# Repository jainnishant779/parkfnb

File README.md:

# ParkFNB

Smart parking for India: owners list their space, drivers book it, and a camera + barrier
at the gate lets the right car in automatically.

## Repo layout

| Folder | What lives here |
|---|---|
| [`research/`](research/) | Market and tech studies, product requirements, pitch deck, proposals, status reports |
| [`hardware/`](hardware/) | ESP32 barrier firmware and the deployment / hardware plan |
| [`ai/`](ai/) | ANPR (number-plate + bay detection) service and its experiments, parking space optimizer |
| [`software/`](software/) | Consumer and owner apps, admin panel, landing page, marketing website, Node backend |

Start with [`software/README.md`](software/README.md) for how to run the apps and backend,
and [`software/docs/system-design.md`](software/docs/system-design.md) for the architecture.

Secrets (`.env`, keys, model weights) are never committed â€” see [`.gitignore`](.gitignore).

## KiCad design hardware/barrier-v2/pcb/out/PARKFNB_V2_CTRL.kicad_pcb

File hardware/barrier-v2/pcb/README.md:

# PARKFNB V2 controller PCB

100 x 80 mm, 2 layers, all through-hole. ESP32 DevKit V1 + 74AHCT125 level shift + sense/protection for the IBT-2.
Motor current does not flow through this board (battery -> fuse -> switch -> IBT-2 directly).

## Files (`out/`)
| File | Use |
|---|---|
| `PARKFNB_V2_Controller_PCB.pdf` | 7 sheets: spec, schematic, top/bottom views, drill table, wiring, bring-up, netlist |
| `PARKFNB_V2_CTRL.kicad_pcb` | KiCad 8 board (placed + routed, GND plane as an unfilled zone) |
| `gerbers/`, `PARKFNB_V2_CTRL_gerbers.zip` | Gerber + Excellon drill, ready for a fab |
| `PARKFNB_V2_CTRL_BOM.csv`, `..._netlist.csv` | BOM and netlist |

## Rebuild
```
pip install shapely numpy matplotlib kiutils gerbonara
python build.py     # route + DRC + export + verify
python report.py    # also rebuilds the PDF
```
Edit `placement.py` (positions) or `design.py` (parts, nets, footprints) and re-run.

## What was verified (and what was not)
Verified here: own DRC (clearance 0.25, edge, annular ring, hole-to-hole, keep-outs, opens, GND plane), the
`.kicad_pcb` parsed with kiutils and connectivity rebuilt independently (no shorts / opens), every Gerber and drill
file re-read with gerbonara and rendered.

NOT verified: KiCad itself was not available. Open the board in KiCad, press **B** (fill zones), run **Inspect > DRC**.
Footprints are generic through-hole footprints from standard pitches: check each one against the real part
(ESP32 header row spacing 25.4 vs 22.86, buzzer pitch, screw terminal, PTC, electrolytics, TVS/diode lead drill).
No thermal, EMC or in-shell test has been done.

## Rev A changes (V2 scope)
- Three position sensors for the 0 - 90 - 180 deg motion: J4 = 0 deg (GPIO32), J10 = 90 deg / locked (GPIO13),
  J5 = 180 deg (GPIO33). All Hall sensors run on 5 V with open-collector outputs pulled up to 3V3.
- Battery = the V1 4 x 18650 holder (assumed 4S, 16.8 V full): TVS P6KE20A, divider 100k/18k (16.8 V -> 2.56 V).
  Input range 7-17 V, so a 2S pack also works.

## Firmware
See sheet 1 of the PDF: new pins are GPIO27 (motor enable), 13/32/33 (0/90/180 deg sensors), 35 (battery ADC),
4 (red LED), 23 (tamper). `config.h` today clamps motion to 0-90 deg; 0-90-180 needs a firmware change.
With a 4S pack limit PWM_MAX to ~180 so the 12 V motor sees ~12 V average.

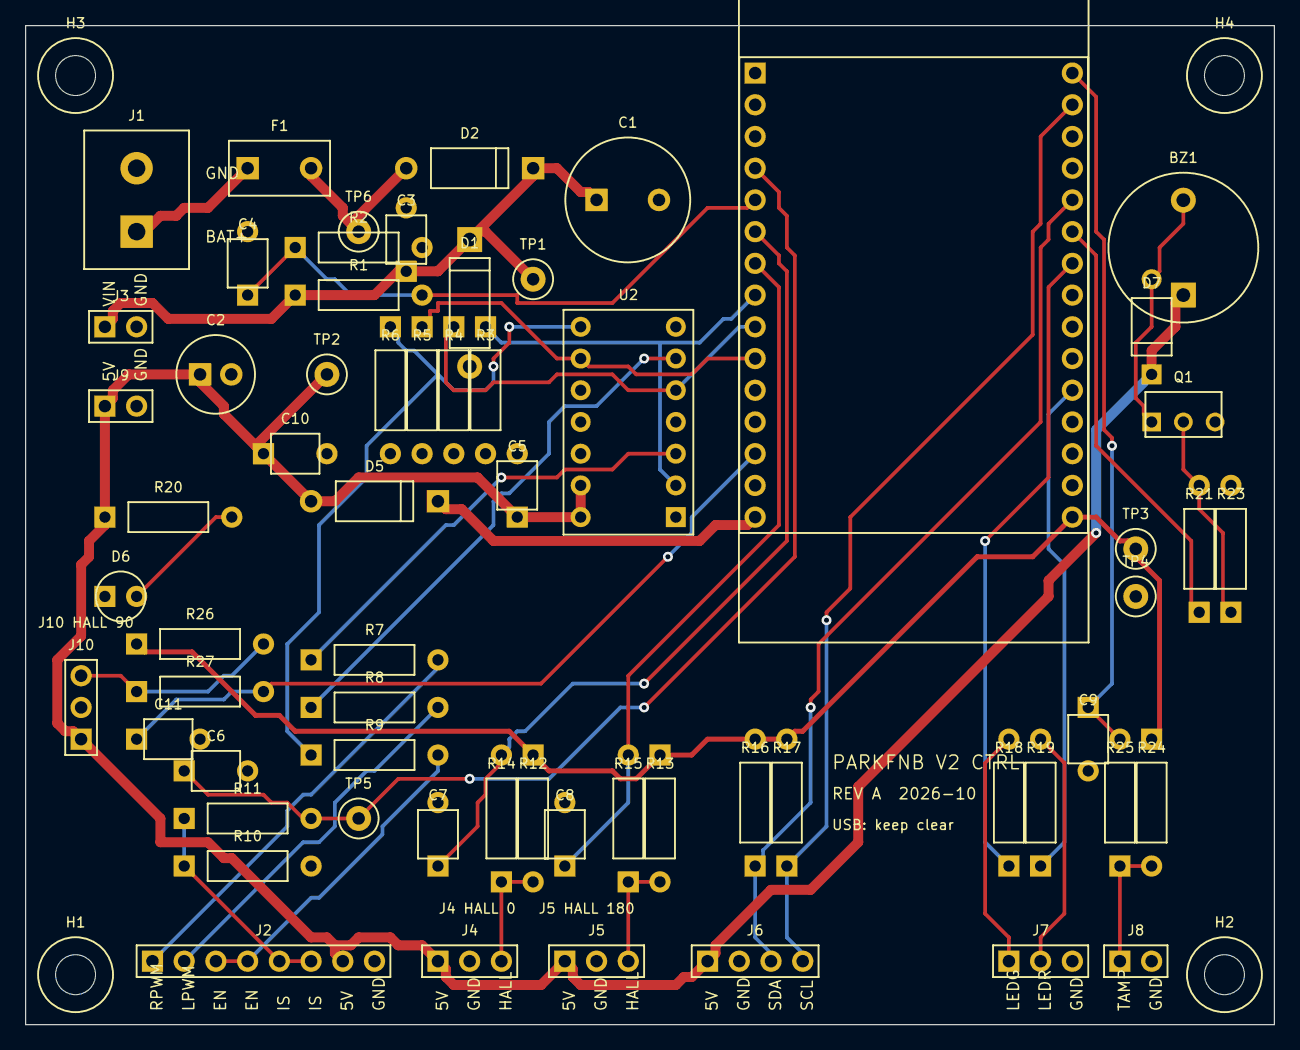
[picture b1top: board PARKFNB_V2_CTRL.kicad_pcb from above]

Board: 2 copper layers, 100.0 x 80.0 mm, 67 parts (0 on the bottom side), 37 nets.

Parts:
BZ1: Buzzer 12mm 5V; BUZZER
C1: 470uF 25V; C470
C2: 220uF 10V; C220
C3, C4, C5, C6, C7, C8, C9, C10, C11: 100nF; C100N
D1: P6KE20A TVS; DO15
D2: 1N5819; D41
D5: 1N5817; D41
D6: LED 3mm green; LED3
D7: 1N4148; D35
ESP1: ESP32 DevKit V1 30-pin; ESP32
F1: PTC 1.1A hold; PTC
H1, H2, H3, H4: M3; MOUNT
J1: BAT IN 7-17V 5.08 2P; SCREW2
J2: IBT-2 CTRL 1x8; HDR8
J3: BUCK IN; HDR2
J4: HALL 0deg 3P; HDR3
J5: HALL 180deg 3P; HDR3
J6: IMU POD 4P; HDR4
J7: STATUS LED 3P; HDR3
J8: TAMPER 2P; HDR2
J9: BUCK OUT; HDR2
J10: HALL 90deg 3P; HDR3
Q1: BC547; TO92
R1: 100k; R
R2: 18k; R
R3, R4, R5, R6, R12, R13, R23, R24, R26: 10k; R
R7, R8, R9: 100R; R
R10: 1k (DNP if IBT-2 has IS resistor); R
R11, R14, R15, R20, R21, R25, R27: 1k; R
R16, R17: 4.7k (DNP if GY-521 has pull-ups); R
R18, R19: 330R; R
TP1: VIN; TP
TP2: +5V; TP
TP3: +3V3; TP
TP4: GND; TP
TP5: ISENSE_F; TP
TP6: VBAT_F; TP
U2: 74AHCT125N; DIP14

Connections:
+3V3: ESP1.30, R12.1, R13.1, R16.2, R17.2, R24.1, R26.1, TP3.1
+5V: BZ1.1, C2.1, C5.1, C10.1, D5.2, D7.1, J2.7, J4.1, J5.1, J6.1, J9.1, J10.1, R20.1, TP2.1, U2.13, U2.14
+5V_ESP: D5.1, ESP1.15
BUZ_B: Q1.2, R21.2, R23.1
BUZ_C: BZ1.2, D7.2, Q1.1
BUZ_DRV: ESP1.21, R21.1
EN_BUF: R6.1, R9.1, U2.8
EN_IN: ESP1.10, R5.1, U2.9
GND: C1.2, C2.2, C3.2, C4.2, C5.2, C6.2, C7.2, C8.2, C9.2, C10.2, C11.2, D1.2, D6.1, ESP1.14, ESP1.29, J1.2, J2.8, J3.2, J4.2, J5.2, J6.2, J7.3, J8.2, J9.2, J10.2, Q1.3, R2.2, R3.2, R4.2, R5.2, R6.2, R10.2, R23.2, TP4.1, U2.1, U2.4, U2.7, U2.10, U2.12
HALL_0: C7.1, ESP1.6, R14.2
HALL_0_RAW: J4.3, R12.2, R14.1
HALL_90: C11.1, ESP1.13, R27.2
HALL_90_RAW: J10.3, R26.2, R27.1
HALL_180: C8.1, ESP1.7, R15.2
HALL_180_RAW: J5.3, R13.2, R15.1
ISENSE: J2.5, J2.6, R10.1, R11.1
ISENSE_F: C6.1, ESP1.4, R11.2, TP5.1
LED_G: ESP1.22, R18.1
LED_G_A: J7.1, R18.2
LED_PWR_A: D6.2, R20.2
LED_R: ESP1.26, R19.1
LED_R_A: J7.2, R19.2
LPWM: J2.2, R8.2
MOT_EN: J2.3, J2.4, R9.2
PWM_L_BUF: R8.1, U2.6
PWM_L_IN: ESP1.9, R4.1, U2.5
PWM_R_BUF: R7.1, U2.3
PWM_R_IN: ESP1.8, R3.1, U2.2
RPWM: J2.1, R7.2
SCL: ESP1.17, J6.4, R17.1
SDA: ESP1.20, J6.3, R16.1
TAMPER: C9.1, ESP1.16, R25.2
TAMPER_RAW: J8.1, R24.2, R25.1
VBAT: F1.1, J1.1
VBAT_F: D2.2, F1.2, TP6.1
VIN: C1.1, C3.1, D1.1, D2.1, J3.1, R1.1, TP1.1
VSENSE: C4.1, ESP1.5, R1.2, R2.1

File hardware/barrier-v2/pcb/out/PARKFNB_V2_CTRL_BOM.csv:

References,Value,"Footprint (generic THT, verify)",Qty,Note
BZ1,Buzzer 12mm 5V,BUZZER,1,
C1,470uF 25V,C470,1,
C2,220uF 10V,C220,1,
"C3, C4, C5, C6, C7, C8, C9, C10, C11",100nF,C100N,9,
D1,P6KE20A TVS,DO15,1,
D2,1N5819,D41,1,
D5,1N5817,D41,1,
D6,LED 3mm green,LED3,1,
D7,1N4148,D35,1,
ESP1,ESP32 DevKit V1 30-pin,ESP32,1,
F1,PTC 1.1A hold,PTC,1,
J1,BAT IN 7-17V 5.08 2P,SCREW2,1,
J10,HALL 90deg 3P,HDR3,1,
J2,IBT-2 CTRL 1x8,HDR8,1,
J3,BUCK IN,HDR2,1,
J4,HALL 0deg 3P,HDR3,1,
J5,HALL 180deg 3P,HDR3,1,
J6,IMU POD 4P,HDR4,1,
J7,STATUS LED 3P,HDR3,1,
J8,TAMPER 2P,HDR2,1,
J9,BUCK OUT,HDR2,1,
Q1,BC547,TO92,1,
R1,100k,R,1,
R10,1k,R,1,DNP-check: fit only if the module does not already have it
"R16, R17",4.7k,R,2,DNP-check: fit only if the module does not already have it
"R18, R19",330R,R,2,
R2,18k,R,1,
"R11, R14, R15, R20, R21, R25, R27",1k,R,7,
"R3, R4, R5, R6, R12, R13, R23, R24, R26",10k,R,9,
"R7, R8, R9",100R,R,3,
TP1,VIN,TP,1,
TP2,+5V,TP,1,
TP3,+3V3,TP,1,
TP4,GND,TP,1,
TP5,ISENSE_F,TP,1,
TP6,VBAT_F,TP,1,
U2,74AHCT125N,DIP14,1,

OFF-BOARD,LM2596 buck module set to 5.1 V,wire to J3 / J9,1,set output BEFORE connecting J9
OFF-BOARD,IBT-2 (BTS7960) module,J2 (8 wires),1,"power B+/B- direct from battery switch, not through this PCB"
OFF-BOARD,GY-521 (MPU6050) pod,J6,1,
OFF-BOARD,A3144 / US5881 Hall sensor + magnet,"J4, J10, J5",3,"5 V supply, open-collector output; 0 / 90 / 180 deg"
OFF-BOARD,Status LED pair (green + red) + 330R on board,J7,1,common cathode on J7.3
OFF-BOARD,Lid tamper micro-switch,J8,1,normally open to GND

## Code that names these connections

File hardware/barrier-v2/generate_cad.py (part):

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    wire([(74, yb), (110, yb), (110, yt), (140, yt)], BLU, 0.7, lab)
wire([(228, 150), (262, 150)], BLU, 0.7, "GPIO18 / 4")
wire([(262, 122), (228, 122)], BLU, 0.7, "GPIO23")
pins = [("GPIO25", "RPWM (raise)", "PIN_MOTOR_IN1 25"), ("GPIO26", "LPWM (lower)", "PIN_MOTOR_IN2 26"),
        ("GPIO27", "IBT-2 EN", "NEW: HIGH while moving"), ("GPIO32", "Hall 0 deg", "NEW"), ("GPIO13", "Hall 90 deg (locked)", "NEW"),
        ("GPIO33", "Hall 180 deg", "NEW"), ("GPIO34", "motor current", "PIN_CURRENT 34"), ("GPIO35", "battery voltage", "NEW"),
        ("GPIO21/22", "IMU SDA / SCL", "unchanged"), ("GPIO18 / 4", "LED green / red", "PIN_LED 18"),
        ("GPIO19", "buzzer", "PIN_BUZZER 19"), ("GPIO23", "tamper", "NEW, optional")]
yy = table(ax, 318, 276, ["PIN", "FUNCTION", "FIRMWARE"], pins, [20, 34, 34], rh=4.3, size=4.8)
note_block(ax, 318, yy - 6, "FIRMWARE (180 deg)", [
    "config.h is set for 0-90 deg today",
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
